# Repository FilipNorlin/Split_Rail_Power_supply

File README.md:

# PFC

# General Continuous-Time State-Space Form

$$
\dot{\mathbf{x}}(t) = A\mathbf{x}(t) + B\mathbf{u}(t)
$$
$$
\mathbf{y}(t) = C\mathbf{x}(t) + D\mathbf{u}(t)
$$

---

$$
	\underbrace{ \left(
		\begin{matrix}
		\dot{x}_{1}(t) \\
		\dot{x}_{2}(t) \\
		\dots \\
		\dot{x}_{n}(t)
		\end{matrix}
	\right) }_{ \dot{x}(t) }
	=
	\underbrace{ \left(
	\begin{matrix}
	A_{11}, A_{12} \dots A_{1n} \\
	A_{21}, A_{22} \dots A_{2n} \\
	\dots \\
	A_{n1}, A_{n2} \dots A_{nn}
	\end{matrix}
	\right) }_{ A }
	\underbrace{ \left(
	\begin{matrix}
	x_{1}(t) \\
	x_{2}(t) \\
	\dots \\
	x_{n}(t)
	\end{matrix}
	\right) }_{ x(t) }
	+ 
	\underbrace{ \left(
	\begin{matrix}
	B_{1} \\
	B_{2} \\
	\dots \\
	B_{n}
	\end{matrix}
	\right) }_{ B }	
	u(t)
$$

$$
y(t) = \underbrace{ [C_{1}, C_{2},\dots C_{n}] }_{ C } 
\underbrace{ \left(
\begin{matrix}
x_{1}(t) \\
x_{2}(t) \\
\dots \\
x_{n}(t)
\end{matrix}
\right) }_{ x(t) }
+
Du(t)
$$

# State Variables

## Large Signal Model

$$
\begin{align}
	x &= 
	\begin{bmatrix}
	i_{L_{A}}(t) \\
	i_{L_{B}}(t) \\
	v_{\text{out}}(t)
	\end{bmatrix}
	& \dot{x} = 
	\begin{bmatrix}
	\dot{i}_{L_{A}}(t) \\
	\dot{i}_{L_{B}}(t) \\
	\dot{v}_{\text{out}}(t)
	\end{bmatrix}
	&& u=v_{\text{in}}
	&& y=v_{\text{out}}
\end{align}
$$

The two switches are $180\degree$ out of phase. This means that the system will have 4 different states of operation. There will be a point where $\text{q}_{\text{A}}$ will be high and $\text{q}_{B}$ low and vise versa, if $\text{D}>0.5$ there will also be a point where both $\text{q}_{\text{A}}$ and $\text{q}_{B}$ will be high simultaneously. If $D < 0.5$  there will be a point where $\text{q}_{\text{A}}$ and $\text{q}_{\text{B}}$ both will be low simultaneously. This makes 4 states:

#### State 1: $\text{q}_{\text{A}}$ & $\text{q}_{\text{B}}$ are high

$$
\begin{align}
v_{L_{A}}(t) &= L \frac{di_{\text{L}_{A}}(t)}{dt} \implies \frac{di_{\text{L}_{A}}(t)}{dt} = \frac{v_{\text{in}}(t)}{L} \\ \\
v_{L_{B}}(t) &= L \frac{di_{\text{L}_{B}}(t)}{dt} \implies \frac{di_{\text{L}_{B}}(t)}{dt} = \frac{v_{\text{in}}(t)}{L} \\ \\
i_{c}(t) &= C \frac{d v_{c}(t)}{dt} \implies \frac{d v_{c}(t)}{dt} = \frac{i_{c}(t)}{C} = -\frac{v_{\text{out}}(t)}{RC}
\end{align}
$$

Both switches are turned on thus both inductors are getting magnetized. The capacitor isnt being charged at this point by any inductor meaning that it is only being discharged to the load, hence why the current is negative.

#### State 2: $\text{q}_{\text{A}}$ high & $\text{q}_{\text{B}}$ low

$$
\begin{align}
v_{L_{A}}(t) &= L \frac{di_{\text{L}_{A}}(t)}{dt} \implies \frac{di_{\text{L}_{A}}(t)}{dt} = \frac{v_{\text{in}}(t)}{L} \\ \\
v_{L_{B}}(t) &= L \frac{di_{\text{L}_{B}}(t)}{dt} \implies \frac{di_{\text{L}_{B}}(t)}{dt} = \frac{v_{\text{in}}(t) - v_{\text{out}}(t)}{L} \\ \\
i_{c}(t) &= C \frac{d v_{c}(t)}{dt} \implies \frac{d v_{c}(t)}{dt} = \frac{i_{c}(t)}{C} = \frac{i_{\text{L}_{B}}(t)}{C} -\frac{v_{\text{out}}(t)}{RC}
\end{align}
$$

Inductor A is still getting magnetized while inductor B is getting demagnetized. The energy from inductor B is being used to charge the output capacitor. 

#### State 3: $\text{q}_{\text{A}}$ low & $\text{q}_{\text{B}}$ high

$$
\begin{align}
v_{L_{A}}(t) &= L \frac{di_{\text{L}_{A}}(t)}{dt} \implies \frac{di_{\text{L}_{A}}(t)}{dt} = \frac{v_{\text{in}}(t) - v_{\text{out}}(t)}{L} \\ \\
v_{L_{B}}(t) &= L \frac{di_{\text{L}_{B}}(t)}{dt} \implies \frac{di_{\text{L}_{B}}(t)}{dt} = \frac{v_{\text{in}}(t)}{L} \\ \\
i_{c}(t) &= C \frac{d v_{c}(t)}{dt} \implies \frac{d v_{c}(t)}{dt} = \frac{i_{c}(t)}{C} = \frac{i_{\text{L}_{A}}(t)}{C} -\frac{v_{\text{out}}(t)}{RC}
\end{align}
$$

Now Inductor B is getting magnetized while inductor A is getting demagnetized. The energy from inductor A is being used to charge the output capacitor. 

#### State 4: $\text{q}_{\text{A}}$ low & $\text{q}_{\text{B}}$ low

$$
\begin{align}
v_{L_{A}}(t) &= L \frac{di_{\text{L}_{A}}(t)}{dt} \implies \frac{di_{\text{L}_{A}}(t)}{dt} = \frac{v_{\text{in}}(t) - v_{\text{out}}(t)}{L} \\ \\
v_{L_{B}}(t) &= L \frac{di_{\text{L}_{B}}(t)}{dt} \implies \frac{di_{\text{L}_{B}}(t)}{dt} = \frac{v_{\text{in}}(t) - v_{\text{out}}(t)}{L} \\ \\
i_{c}(t) &= C \frac{d v_{c}(t)}{dt} \implies \frac{d v_{c}(t)}{dt} = \frac{i_{c}(t)}{C} = \frac{i_{\text{L}_{A}}(t) + i_{\text{L}_{B}}(t)}{C} -\frac{v_{\text{out}}(t)}{RC}
\end{align}
$$

In this last state both the switches are off meaning that both the inductors are getting demagnetized into the capacitor. Having two or more inductors switching with some offset will make the capacitor get charged more frequently thus reducing the voltage ripple on the output.

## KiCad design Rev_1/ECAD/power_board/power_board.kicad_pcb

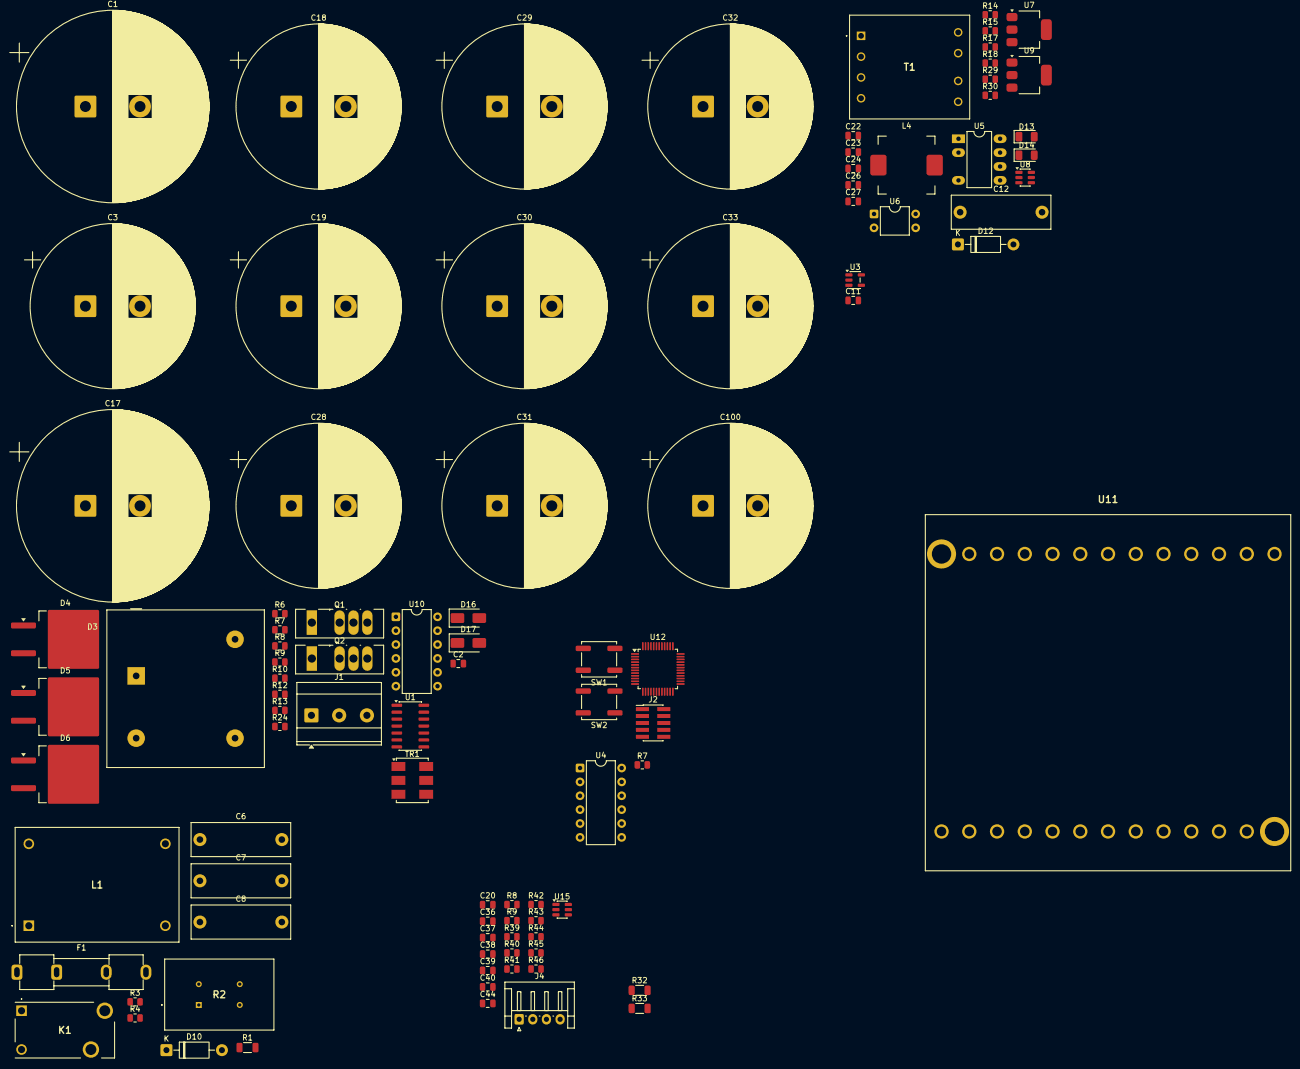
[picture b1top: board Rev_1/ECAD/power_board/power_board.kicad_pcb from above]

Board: 2 copper layers, 96 parts (0 on the bottom side), 57 nets, no tracks yet.

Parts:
C1, C17: 680u; CP_Radial_D35.0mm_P10.00mm_SnapIn
C2: 1u; C_0805_2012Metric
C3, C18, C19, C28, C29, C30, C31, C32, C33, C100: 2m2; CP_Radial_D30.0mm_P10.00mm_SnapIn
C6: 100n; C_Rect_L18.0mm_W6.0mm_P15.00mm_FKS3_FKP3
C7, C8: 2n2; C_Rect_L18.0mm_W6.0mm_P15.00mm_FKS3_FKP3
C11, C20, C36, C37, C38, C40, C44: 100n; C_0805_2012Metric
C12: 2n2, 250VAC; C_Rect_L18.0mm_W6.0mm_P15.00mm_FKS3_FKP3
C22, C26: 10u; C_0805_2012Metric
C23, C27: 22u; C_0805_2012Metric
C24: 100n, 16V; C_0805_2012Metric
C39: 4u7; C_0805_2012Metric
D3: KBPC3510W; Diode_Bridge_GeneSiC_KBPC_W
D4, D5, D6: schottky; TO-263-2
D10, D12: 1N4007; D_DO-41_SOD81_P10.16mm_Horizontal
D13, D14: D_Schottky; D_1206_3216Metric
D16, D17: BYG20J; D_SMA
F1: T6A3; Fuseholder_Clip-5x20mm_Keystone_3512_Inline_P23.62x7.27mm_D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
J1: Screw_Terminal_01x03; TerminalBlock_Phoenix_MKDS-3-3-5.08_1x03_P5.08mm_Horizontal
J2: Conn_ARM_JTAG_SWD_10; PinHeader_2x05_P1.27mm_Vertical_SMD
J4: Conn_01x04_Pin; JST_EH_S4B-EH_1x04_P2.50mm_Horizontal
K1: SPST-NO; Industrial-Relays-OJS-SS-112HEF_SPST-NO
L1: 2m2; Common_Mode_Choke_2Line
L4: 6u8; Inductor_SMD_Pulse_BPSC_10.5x10.3mm
Q1, Q2: IPZA60R070CM8XKSA1; TO-247-4_Vertical
R1: 22; R_1206_3216Metric
R2: 27; Resistor_THT_Power_Axial_WW20W_P27mm
R3, R15: 1k; R_0805_2012Metric
R4, R7, R7#2, R8, R8#2, R9, R12, R13, R24: 10k; R_0805_2012Metric
R6, R9#2, R30: 4k7; R_0805_2012Metric
R10: 3k3; R_0805_2012Metric
R14: 3.6M; R_0805_2012Metric
R17: 390 1/8W; R_0805_2012Metric
R18: 2k 1/8W; R_0805_2012Metric
R29: 34k; R_0805_2012Metric
R32, R33: 10k; R_1206_3216Metric
R39, R40, R41, R42, R43, R44, R45, R46: 5k1; R_0805_2012Metric
SW1, SW2: SW_Push; SW_Push_1P1T_NO_CK_KSC6xxJ
T1: 063932
TR1: ADT1-1WT; Mini-Circuits_CD542_H2.84mm
U1: UCC27714D; SOIC-14_3.9x8.7mm_P1.27mm
U3: INA180A4; SOT-23-5
U4, U10: PC837; DIP-12_W7.62mm
U5: TNY274P; PowerIntegrations_PDIP-8C
U6: PC817; DIP-4_W7.62mm
U7: 5V LDO; SOT-223-3_TabPin2
U8: LMR51430; SOT-23-6
U9: 3v3 LDO; SOT-223-3_TabPin2
U11: B66398W1024T1; ETD59
U12: STM32F103C8Tx; LQFP-48_7x7mm_P0.5mm
U15: USBLC6-2SC6; SOT-23-6

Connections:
+3V3_Secondary: C20.1, C27.1, C36.1, C37.1, C38.1, C39.1, C44.1, J2.1 (VTref), R8.1, R24.1, SW2.1, U9.3 (OUT), U12.9 (VDDA), U12.24 (VDD), U12.36 (VDD), U12.48 (VDD)
+5V: C11.1, U3.5 (V+)
+5V_Primary: C23.1, R6.1, R7.1, R9#2.1, R12.1, R13.1, U7.3 (OUT)
+5V_Secondary: C26.1, U9.1 (IN)
+12V: D10.1 (K), R1.1
+12V_Secondary: C22.1, D14.1 (K), U7.1 (IN), U8.3 (VIN), U8.5 (EN)
+70V: C18.1, C28.1, C30.1, C32.1, C100.1, R32.1
-70V: C3.2, C19.2, C29.2, C31.2, C33.2, R33.2
/AC_L: F1.1, J1.1
/AC_N: C6.2, J1.2, L1.2
/EN/NC: R7.2, R9#2.2, U1.4 (EN/NC), U4.8
/GATE_DRIVER_HI: R12.2, U1.1 (HI), U10.12
/GATE_DRIVER_LI: R13.2, U1.2 (LI), U10.10
/HS: D17.2 (A), Q2.3 (DS), U1.11 (HS)
/H_SW_NODE: Q2.2 (S), TR1.3
/Input Filter And Slow Start/AC_L_OUT: D3.4, K1.4 (NO), R2.2
/Input Filter And Slow Start/AC_N_OUT: C8.1, D3.2, L1.3
/Input Filter And Slow Start/COIL_GATE: R3.1, R4.1
/Input Filter And Slow Start/L_FILTERED: C7.1, K1.3 (COM), L1.4, R2.1
/LS: Q1.3 (DS), U1.5 (COM)
/L_SW_NODE: Q1.1 (D), TR1.1
/MCU/BOOT0: R8.2, R9.1, SW2.2, U12.44 (BOOT0)
/MCU/D+: U15.3 (I/O2), U15.4 (I/O2)
/MCU/D-: U15.1 (I/O1), U15.6 (I/O1)
/MCU/MISO: J4.3, U12.27 (PB14)
/MCU/MOSI: J4.4, U12.28 (PB15)
/MCU/SCK: J4.2, U12.26 (PB13)
/MCU/SWCLK: J2.4 (SWCLK/TCK), U12.37 (PA14)
/MCU/SWDIO: J2.2 (SWDIO/TMS), U12.34 (PA13)
/MCU/~RST: C40.1, J2.10 (~RESET), SW1.2, U12.7 (NRST)
/MCU/~SS: J4.1, U12.25 (PB12)
/Startup Power/BOOTSTRAP: C24.1, U8.6 (CB)
/Startup Power/BUCK_5V: L4.2, R29.1
/Startup Power/FB: R29.2, R30.1, U8.4 (FB)
/Startup Power/SW: C24.2, L4.1, U8.2 (SW)
/VREF: C2.1, R6.2, R10.1
/~ENABLE_GATE_DRIVER: U4.5, U10.3
Earth_Protective: C7.2, C8.2, J1.3
GND1: C1.2, C17.2, D3.3 (-), U5.5 (S), U5.6 (S), U5.7 (S), U5.8 (S), U6.3
GND2: D6.1 (A), D6.3 (K), TR1.2
unnamed: C6.1, F1.2, L1.1
unnamed: C3.1, C18.2, C19.1, C28.2, C29.1, C30.2, C31.1, C32.2, C33.1, C100.2, R32.2, R33.1
unnamed: D4.1 (A), D4.3 (K), TR1.6
unnamed: D4.2 (K), D5.2 (K), D6.2 (K)
unnamed: D5.3 (K), TR1.4
unnamed: D10.2 (A), K1.1 (COIL_1)
unnamed: D12.2 (A), T1.4, U5.4 (D)
unnamed: D12.1 (K), R15.2
unnamed: D13.2 (A), T1.5
unnamed: D14.2 (A), T1.6
unnamed: D16.1 (K), U1.13 (HB)
unnamed: K1.2 (COIL_2), R1.2
unnamed: R17.2, R18.1, U6.1
unnamed: R14.2, U5.1 (EN/UV), U6.4
PRIM_SGND: C2.2, C11.2, C12.2, C22.2, C23.2, R4.2, R7#2.2, R8#2.2, R10.2, R18.2, T1.8, U1.3 (VSS), U3.2 (GND), U4.7, U6.2, U7.2 (GND), U10.9, U10.11
SEC_SGND: C20.2, C26.2, C27.2, C36.2, C37.2, C38.2, C39.2, C40.2, C44.2, J2.3 (GND), J2.5 (GND), J2.9 (GNDDetect), R9.2, R30.2, SW1.1, T1.7, U4.6, U8.1 (GND), U9.2 (GND), U10.2, U10.4, U12.8 (VSSA), U12.23 (VSS), U12.35 (VSS), U12.47 (VSS), U15.2 (GND)
VBUS: C1.1, C12.1, C17.1, D3.1 (+), Q2.1 (D), R14.1, T1.1

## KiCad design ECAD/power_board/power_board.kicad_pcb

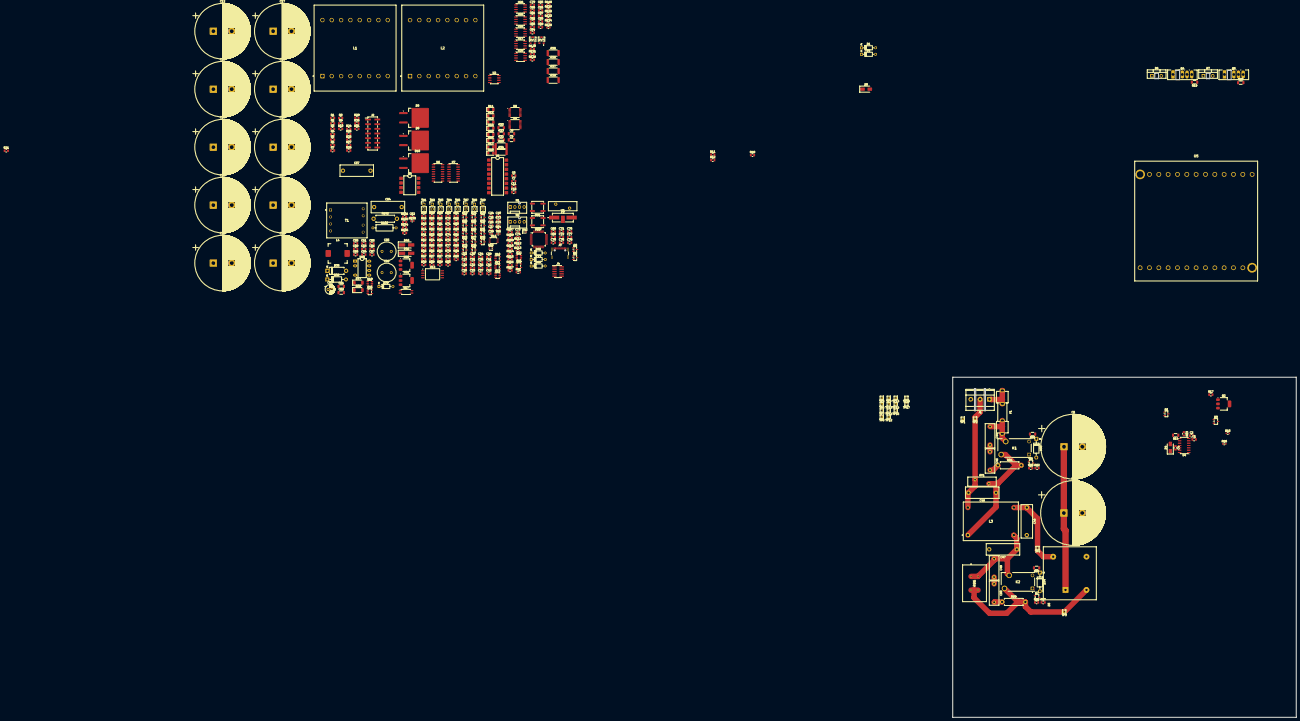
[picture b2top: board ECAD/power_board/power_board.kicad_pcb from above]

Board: 4 copper layers, 346 parts (0 on the bottom side), 217 nets.

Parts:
C1, C4, C6, C7, C10, C11, C28, C29, C34, C35, C38, C42, C43, C68, C69, C70, C71, C75, C76, C77, C78, C79, C82, C85, C86, C87: 100n; C_0805_2012Metric
C2, C22, C23, C30, C31, C32, C33, C36, C37, C41, C63, C65, C66, C80, C81, C84, C88, C89: 1u; C_0805_2012Metric
C3, C5: 680u; CP_Radial_D35.0mm_P10.00mm_SnapIn
C8, C9: C_Small; C_1206_3216Metric
C12, C13, C14, C15, C16, C17, C18, C19, C20, C21: 2m2; CP_Radial_D30.0mm_P10.00mm_SnapIn
C24, C25, C26, C27: TBD; C_0603_1608Metric
C39, C40: 300p; C_0603_1608Metric
C44, C45, C49, C50: 100n, >230Vac; C_Rect_L13.0mm_W5.0mm_P10.00mm_FKS3_FKP3_MKS4
C46: 100n, >230AC; C_Rect_L18.0mm_W6.0mm_P15.00mm_FKS3_FKP3
C47, C48, C57: 2n2; C_Rect_L18.0mm_W6.0mm_P15.00mm_FKS3_FKP3
C51: 10n, 1kV; C_1206_3216Metric
C52: 100n, 50V; C_0603_1608Metric
C53: 10u, 50V; CP_Radial_D5.0mm_P2.00mm
C54: 2n2, 250VAC; C_Rect_L18.0mm_W6.0mm_P15.00mm_FKS3_FKP3
C55, C56: 470u; C_Radial_D10.0mm_H16.0mm_P5.00mm
C58: 4u7, 20V; C_0805_2012Metric
C59, C64, C83: 10u; C_0805_2012Metric
C60, C67: 22u; C_0805_2012Metric
C61: 100n, 16V; C_0805_2012Metric
C62: 47u; C_1206_3216Metric
C72: 4u7; C_0805_2012Metric
C73, C74: 27p; C_0603_1608Metric
D1, D2, D43, D44, D45: 1N4148; D_DO-35_SOD27_P7.62mm_Horizontal
D3: KBPC3510W; Diode_Bridge_GeneSiC_KBPC_W
D4, D5: BYG20J; D_SMA
D6, D7: D; TO-220-2_Vertical
D8, D9, D10: schottky; TO-263-2
D11, D12, D13, D14, D15, D16, D17, D18: LED; LED_1206_3216Metric
D19, D20, D21, D22, D23, D24, D25, D26, D27, D28, D29, D30, D31, D32: BAT54S; SOT-23
D33, D34, D36: 1N4007; D_DO-41_SOD81_P10.16mm_Horizontal
D35: P6KE150A; D_DO-15_P10.16mm_Horizontal
D37, D38: SB24; D_SOD-128
D39: BZX79-C11; D_DO-35_SOD27_P7.62mm_Horizontal
D40, D41: SK15; D_SMA_Handsoldering
D42: TVS; D_SOD-523
F1: T6A3; Fuseholder_Clip-5x20mm_Keystone_3512_Inline_P23.62x7.27mm_D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
F2: Polyfuse; RV_Disc_D15.5mm_W5mm_P7.5mm
FB1: 120R; L_0805_2012Metric
J1: Screw_Terminal_01x03; TerminalBlock_Phoenix_MKDS-3-3-5.08_1x03_P5.08mm_Horizontal
J2: Conn_02x07_Odd_Even; PinHeader_2x07_P2.54mm_Vertical_SMD
J3: USB_C_Receptacle_USB2.0_16P; USB_C_Receptacle_GCT_USB4105-xx-A_16P_TopMnt_Horizontal
J4: Conn_ARM_JTAG_SWD_10; PinHeader_2x05_P1.27mm_Vertical_SMD
K1, K2: SPST-NO; Industrial-Relays-OJS-SS-112HEF_SPST-NO
L1, L2: 220u; ETD-39-Inductor
L3: 2m2; Common_Mode_Choke_2Line
L4: 6u8; Inductor_SMD_Pulse_BPSC_10.5x10.3mm
M1, M2: Fan_4pin; FanPinHeader_1x04_P2.54mm_Vertical
Q1: NPN; SOT-23
Q2: NMOS; SOT-223-3_TabPin2
Q3, Q6, Q7: NMOS; SOT-23-3
Q4, Q5: IPZA60R070CM8XKSA1; TO-247-4_Vertical
Q8, Q9: 2N7002; SOT-23
R1, R2, R3, R4, R5: 330; R_0805_2012Metric
R6, R7, R8, R9, R10, R49, R50, R51, R52, R53, R54, R76, R92, R97, R101, R120, R126: 1k; R_0805_2012Metric
R11, R106: 4k7; R_0805_2012Metric
R12, R121: 100k; R_0805_2012Metric
R13: 5; R_0805_2012Metric
R14: 2.2; R_1206_3216Metric
R15, R16: 0; R_0603_1608Metric
R17, R18: 470; R_0805_2012Metric
R19, R20: 3, 1W; R_1206_3216Metric
R21: 10m; R_0805_2012Metric
R22, R23: R_Small; R_1206_3216Metric
R24, R25, R26, R27, R28, R29, R30, R31, R109, R110: 5k1; R_0805_2012Metric
R32: 15m; R_1206_3216Metric
R33, R34, R35, R36, R37, R38: 10k, 1W; R_2512_6332Metric
R39, R40, R45, R46, R47, R48, R55, R56, R57, R58, R59, R63, R64, R65, R66, R67, R70, R71, R72, R74, R77, R78, R88, R89, R90: 3k3; R_0805_2012Metric
R41, R42, R43, R44: 100; R_0805_2012Metric
R60, R61, R62, R85, R86, R87: 27k; R_0805_2012Metric
R68, R69, R93, R98, R107, R108, R114, R115, R116, R117: 10k; R_0805_2012Metric
R73, R75: 22k; R_0603_1608Metric
R79, R80, R81, R82, R83: 68k; R_0805_2012Metric
R84, R118, R119, R122, R123, R124, R125: R_Small; R_0603_1608Metric
R91, R95: 22; R_1206_3216Metric
R94, R99: 100, >230Vac; R_Axial_DIN0411_L9.9mm_D3.6mm_P12.70mm_Horizontal
R96: 27; Resistor_THT_Power_Axial_WW20W_P27mm
R100: 3.6M, 325V; R_Axial_DIN0309_L9.0mm_D3.2mm_P12.70mm_Horizontal
R102: 100, 325V; R_Axial_DIN0411_L9.9mm_D3.6mm_P12.70mm_Horizontal
R103: 390 1/8W; R_0805_2012Metric
R104: 2k 1/8W; R_0805_2012Metric
R105: 34k; R_0603_1608Metric
R111, R112: 22; R_0603_1608Metric
R113: 1k5; R_0603_1608Metric
RV1: Varistor; RV_Disc_D15.5mm_W5mm_P7.5mm
RV2, RV3: 100k; Potentiometer_SMD_Trimmer_PVG3_3.6x3
SW1, SW2: SW_Push; SW_Push_1P1T_NO_CK_KSC6xxJ
T1: 063932
TH1, TH2, TH3, TH4, TH5, TH7, TH8, TH9: 10k; PinHeader_1x02_P2.54mm_Vertical
TH6: 10k; R_0603_1608Metric
TP1: LIVE_IN; Pin_D0.7mm_L6.5mm_W1.8mm_FlatFork
TP2: NEUTRAL_IN; Pin_D0.7mm_L6.5mm_W1.8mm_FlatFork
TP3: LIVE_OUT; Pin_D0.7mm_L6.5mm_W1.8mm_FlatFork
TP4: NEUTRAL_OUT; Pin_D0.7mm_L6.5mm_W1.8mm_FlatFork
TP5: HG; Pin_D0.7mm_L6.5mm_W1.8mm_FlatFork
TP6: VBUS; Pin_D0.7mm_L6.5mm_W1.8mm_FlatFork
TP7: LG; Pin_D0.7mm_L6.5mm_W1.8mm_FlatFork
TP8: HP; Pin_D0.7mm_L6.5mm_W1.8mm_FlatFork
TP9: LP; Pin_D0.7mm_L6.5mm_W1.8mm_FlatFork
TP10: HS; Pin_D0.7mm_L6.5mm_W1.8mm_FlatFork
TP11: LS; Pin_D0.7mm_L6.5mm_W1.8mm_FlatFork
TP12: +RECT; Pin_D0.7mm_L6.5mm_W1.8mm_FlatFork
TP13: -RECT; Pin_D0.7mm_L6.5mm_W1.8mm_FlatFork
TP14: +70V; Pin_D0.7mm_L6.5mm_W1.8mm_FlatFork
TP15: -70V; Pin_D0.7mm_L6.5mm_W1.8mm_FlatFork
TP16: PRIM_SHUNT_H; Pin_D0.7mm_L6.5mm_W1.8mm_FlatFork
TP17: PRIM_SHUNT_L; Pin_D0.7mm_L6.5mm_W1.8mm_FlatFork
U1: LTV-847S; SMDIP-16_W9.53mm
U2: ISO6720BD; SOIC-8_3.9x4.9mm_P1.27mm
U3: LTV-827S; SMDIP-8_W9.53mm
U4: UCC27714D; SOIC-14_3.9x8.7mm_P1.27mm
U5: ETD59
U6, U7: 74HC595; SOIC-16_3.9x9.9mm_P1.27mm
U8, U9: NMUX1308PW; TSSOP-16_4.4x5mm_P0.65mm
U10: INA180A2; SOT-23-5
U11: INA180A1; SOT-23-5
U12: AMC1350; SOT-23-6
U13: AMC1350DWV; SOIC-8_7.5x5.85mm_P1.27mm
U14: LM358; TSSOP-8_3x3mm_P0.65mm
U15: TLV6001DCK; SOT-353_SC-70-5
U16: TNY274P; PowerIntegrations_PDIP-8C
U17: PC817; SOP-4_4.4x2.6mm_P1.27mm
U18: 5V LDO; SOT-223-3_TabPin2
U19: LMR51430; SOT-23-6
U20: TPS60403DBV; SOT-23-5
U21: 3v3 LDO; SOT-223-3_TabPin2
U22: USBLC6-2SC6; SOT-23-6
U23: STM32F103C8Tx; LQFP-48_7x7mm_P0.5mm
U24: TPS3823-xxDBV; SOT-23-5
U25, U25#2, U27, U28: LMV393; SOIC-8_3.9x4.9mm_P1.27mm
U26: NE555D; SOIC-8_3.9x4.9mm_P1.27mm
Y1: 8MHz; HC-49US

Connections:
+3V3_Secondary: C6.1, C7.1, C10.1, C11.1, C29.1, C35.1, C67.1, C68.1, C69.1, C70.1, C71.1, C72.1, C78.1, C86.1, C87.1, D19.2 (K), D20.2 (K), D21.2 (K), D22.2 (K), D23.2 (K), D24.2 (K), D25.2 (K), D27.2 (K), D28.2 (K), D29.2 (K), D30.2 (K), D31.2 (K), J4.1 (VTref), R9.1, R10.1, R39.1, R40.1, R47.1, R48.1, R57.1, R58.1, R66.1, R67.1, R77.1, R107.1, R113.1, R122.1, R124.1, RV3.1, SW2.1, U2.1 (VCC1), U6.10 (~SRCLR), U6.16 (VCC), U7.10 (~SRCLR), U7.16 (VCC), U8.16 (V_{CC}), U9.16 (V_{CC}), U11.5 (V+), U14.8 (V+), U15.5 (V+), U21.3 (OUT), U23.9 (VDDA), U23.24 (VDD), U23.36 (VDD), U23.48 (VDD), U24.5 (V_{DD}), U27.8 (V+), U28.8 (V+)
+5V_Primary: C28.1, C60.1, C79.1, C82.1, C85.1, D32.2 (K), R6.1, R7.1, R8.1, R118.1, R121.1, RV2.1, U2.8 (VCC2), U10.5 (V+), U12.5 (S), U13.1 (VDD1), U18.3 (OUT), U25.8 (V+), U25#2.8 (V+), U26.4 (~RST), U26.8 (VCC)
+5V_Secondary: C62.1, C63.1, C64.1, D40.1 (K), D41.1 (K), R116.1, R117.1, U13.8 (VDD2), U20.2 (IN), U21.1 (IN)
+5V_USB: C77.1, D40.2 (A), FB1.2
+12V_Primary: C55.1, C59.1, D33.1 (K), D34.1 (K), D37.1 (K), D39.1 (K), R13.1, R91.1, R95.1, U18.1 (IN)
+12V_Secondary: C56.1, C58.1, D38.1 (K), M1.2 (+), M2.2 (+), U19.3 (VIN), U19.5 (EN)
+70V: C12.1, C14.1, C16.1, C18.1, C20.1, L1.2, R33.1, R35.1, R37.1, R85.1, TP14.1 (1_1)
-5V: C38.1, C66.1, D26.1 (A), U14.4 (V-), U20.1 (OUT)
-70V: C13.2, C15.2, C17.2, C19.2, C21.2, L2.2, R34.2, R36.2, R38.2, R62.1, TP15.1 (1_1)
/AC_L: F1.1, J1.1, TP1.1 (1_1)
/AC_N: C46.2, J1.2, L3.2, RV1.2, TP2.1 (1_1)
/Current Sensing/+: C25.1, R41.2, U11.3 (+)
/Current Sensing/-: C27.1, R42.2, U11.4 (-)
/Current Sensing/AD_TEMP_BOARD: D25.3 (COM), R64.2, U8.13 (Y0)
/Current Sensing/AD_TEMP_DIODE1: D19.3 (COM), R45.2, U8.14 (Y1)
/Current Sensing/AD_TEMP_DIODE2: D22.3 (COM), R55.2, U8.15 (Y2)
/Current Sensing/AD_TEMP_DIODE3: D24.3 (COM), R63.2, U8.12 (Y3)
/Current Sensing/AD_TEMP_DIODE_PRIM1: D27.3 (COM), R70.2, U8.4 (Y7)
/Current Sensing/AD_TEMP_DIODE_PRIM2: D30.3 (COM), R78.2, U9.13 (Y0)
/Current Sensing/AD_TEMP_NMOS_HS: D23.3 (COM), R56.2, U8.1 (Y4)
/Current Sensing/AD_TEMP_NMOS_LS: D20.3 (COM), R46.2, U8.5 (Y5)
/Current Sensing/AD_TEMP_TANSFORMER: D28.3 (COM), R71.2, U8.2 (Y6)
/Current Sensing/HW Protection/PRIM_CURRENT_VREF: C81.1, RV2.2, U25.2 (-)
/Current Sensing/HW Protection/SEC_CURRENT_VREF: C88.1, RV3.2, U28.2 (-)
/Current Sensing/HW Protection/~TRIG: U25.1, U26.2 (TRIG)
/Current Sensing/MUX_OUT: C40.1, R75.2, U15.4, U23.10 (ADC1_IN0)
/Current Sensing/PRIMARY_CURRENT_SENSE: R49.1, U10.1
/Current Sensing/PRIMARY_MUX_OUT: U12.4 (A), U13.2 (IN+)
/Current Sensing/PRIM_BUS_VOLTAGE: D32.3 (COM), R89.2, U12.3 (B1), U25.5 (+), U25#2.3 (+)
/Current Sensing/PRIM_CURRENT_SENSE: R49.2, R50.1, U12.1 (B2), U25.3 (+)
/Current Sensing/SECONDARY_CURRENT_SENSE: R52.1, U11.1
/Current Sensing/SEC_CURRENT_SENSE: D21.3 (COM), R52.2, R53.1, U28.3 (+)
/Current Sensing/SEC_NEG_VOLTAGE: D29.3 (COM), R76.2, U27.5 (+)
/Current Sensing/SEC_POS_VOLTAGE: D31.3 (COM), R90.2, U27.3 (+)
/EN/NC: Q1.1 (C), U4.4 (EN/NC)
/GATE_DRIVER_HI: U2.2 (INA), U23.29 (TIM1_CH1)
/GATE_DRIVER_HI_ISO: U2.7 (OUTA), U4.1 (HI)
/GATE_DRIVER_LO: U2.3 (INB), U23.30 (TIM1_CH2)
/GATE_DRIVER_LO_ISO: U2.6 (OUTB), U4.2 (LI)
/HG: Q4.4 (G), R19.2
/HS: C4.1, D5.2 (A), Q4.3 (DS), U4.11 (HS)
/H_SW: R19.1, TP5.1 (1_1), U4.12 (HO)
/H_SW_NODE: D6.1 (K), Q4.2 (S), TP8.1 (1_1), U5.13 (P1)
/Input Filter And Slow Start/AC_L_FILTERED: C47.1, C49.1, K2.3 (COM), L3.4, R96.1
/Input Filter And Slow Start/AC_L_FUSED: C44.1, F1.2, K1.3 (COM)
/Input Filter And Slow Start/AC_L_INPUT_RELAY: C46.1, K1.4 (NO), L3.1, R94.2, RV1.1
/Input Filter And Slow Start/AC_L_OUT: D3.4, K2.4 (NO), R96.2, R99.2, TP3.1 (1_1)
/Input Filter And Slow Start/AC_N_OUT: C48.1, D3.2, L3.3, TP4.1 (1_1)
/Input Filter And Slow Start/AC_RELAY1_RC_SNUBBER_1: C44.2, C45.1
/Input Filter And Slow Start/AC_RELAY1_RC_SNUBBER_2: C45.2, R94.1
/Input Filter And Slow Start/AC_RELAY2_RC_SNUBBER_1: C49.2, C50.1
/Input Filter And Slow Start/AC_RELAY2_RC_SNUBBER_2: C50.2, R99.1
/Input Filter And Slow Start/RELAY1_COIL_2: K1.2 (COIL_2), R91.2
/Input Filter And Slow Start/RELAY2_COIL_2: K2.2 (COIL_2), R95.2
/Input Filter And Slow Start/RELAY_SWITCH_D: D33.2 (A), K1.1 (COIL_1), Q6.1 (D)
/Input Filter And Slow Start/RELAY_SWITCH_G: Q6.2 (G), R92.1, R93.1
/Input Filter And Slow Start/SOFT_SWITCH_D: D34.2 (A), K2.1 (COIL_1), Q7.1 (D)
/Input Filter And Slow Start/SOFT_SWITCH_G: Q7.2 (G), R97.1, R98.1
/LG: Q5.4 (G), R20.2
/LS: Q5.3 (DS), U4.5 (COM)
/L_SW: R16.1, R20.1, TP7.1 (1_1), U4.6 (LO)
/L_SW_NODE: D7.2 (A), Q5.1 (D), TP9.1 (1_1), U5.1 (P2)
/MCU/BOOT0: R107.2, R108.1, SW2.2, U23.44 (BOOT0)
/MCU/CC1: J3.A5 (CC1), R110.1
/MCU/CC2: J3.B5 (CC2), R109.1
/MCU/D+: J3.A6 (D+), J3.B6 (D+), R112.2, R113.2, U22.3 (I/O2), U22.4 (I/O2)
/MCU/D-: J3.A7 (D-), J3.B7 (D-), R111.2, U22.1 (I/O1), U22.6 (I/O1)
/MCU/FAN_PWM_1: Q8.1 (G), R114.1, U23.45 (TIM4_CH3)
/MCU/FAN_PWM_2: Q9.1 (G), R115.1, U23.46 (TIM4_CH4)
/MCU/POLLYFUSED: C76.1, F2.2, FB1.1
/MCU/PWM_1: M1.4 (PWM), Q8.3 (D), R116.2
/MCU/PWM_2: M2.4 (PWM), Q9.3 (D), R117.2
/MCU/RCC_OSC_IN: C73.2, U23.5 (RCC_OSC_IN), Y1.1
/MCU/RCC_OSC_OUT: C74.1, U23.6 (RCC_OSC_OUT), Y1.2
/MCU/STM_D+: R112.1, U23.33 (USB_DP)
/MCU/STM_D-: R111.1, U23.32 (USB_DM)
/MCU/SWCLK: J4.4 (SWCLK/TCK), U23.37 (SYS_JTCK-SWCLK)
/MCU/SWDIO: J4.2 (SWDIO/TMS), U23.34 (SYS_JTMS-SWDIO)
/MCU/TACHO_1: M1.3 (Tacho), U23.40 (TIM3_CH1)
/MCU/TACHO_2: M2.3 (Tacho), U23.41 (TIM3_CH2)
/MCU/TIM1_BKN: D43.1 (K), D44.1 (K), D45.1 (K), U23.16 (TIM1_BKIN)
/MCU/WDI: U23.31 (PA10), U24.4 (WDI)
/MCU/~MR: SW1.2, U24.3 (~MR)
/MCU/~RST: C75.2, J4.10 (~RESET), U23.7 (NRST), U24.1 (~RESET)
/NEG_RECTIFIED: D8.1 (A), D9.1 (A), D10.1 (A), L2.1, R23.2, TP13.1 (1_1)
/NEG_SNUB: C9.2, R23.1
/POS_RECTIFIED: D8.2 (K), D9.2 (K), D10.2 (K), L1.1, R22.2, TP12.1 (1_1)
/POS_SNUB: C8.2, R22.1
/PRIM_MUX_SELECT: R1.1, U23.18 (PB0)
/QH': U6.9 (QH'), U7.14 (SER)
/RCLK: U6.12 (RCLK), U7.12 (RCLK), U23.42 (PB6)
/RELAY_SOFT_SWITCH: R2.1, U23.19 (PB1)
/RELAY_SWITCH: R3.1, U23.20 (PB2)
/S10: U6.15 (QA), U8.11 (S0)
/S11: U6.1 (QB), U8.10 (S1)
/S12: U6.2 (QC), U8.9 (S2)
/S20: U6.4 (QE), U9.11 (S0)
/S21: U6.5 (QF), U9.10 (S1)
/S22: U6.6 (QG), U9.9 (S2)
/SEC_PRIM: C8.1, D8.3 (K), TP10.1 (1_1), U5.14 (S1)
/SEC_SEC: C9.1, D9.3 (K), TP11.1 (1_1), U5.26 (S2)
/SER: U6.14 (SER), U23.21 (PB10)
/SRCLK: U6.11 (SRCLK), U7.11 (SRCLK), U23.22 (PB11)
/Startup Power/AUX_PRIM: D37.2 (A), T1.5
/Startup Power/AUX_SEC: D38.2 (A), T1.6
/Startup Power/BOOTSTRAP: C61.1, U19.6 (CB)
/Startup Power/BUCK_5V: D41.2 (A), L4.2, R105.1
/Startup Power/FB: R105.2, R106.1, U19.4 (FB)
/Startup Power/SW: C61.2, L4.1, U19.2 (SW)
/TEMP_MUX1: U8.3 (Z), U23.14 (ADC1_IN4)
/TEMP_MUX2: U9.3 (Z), U23.15 (ADC1_IN5)
/Y1: J2.1, U9.14 (Y1)
/Y2: J2.3, U9.15 (Y2)
/Y3: J2.5, U9.12 (Y3)
/Y4: J2.7, U9.1 (Y4)
/Y5: J2.9, U9.5 (Y5)
/Y6: J2.11, U9.2 (Y6)
/Y7: J2.13, U9.4 (Y7)
/~E1: U6.3 (QD), U8.6 (~E)
/~E2: U6.7 (QH), U9.6 (~E)
/~PRIM_OCP: R9.2, U3.8, U23.17 (PA7)
/~PRIM_OVP: R10.2, U3.6, U23.38 (PA15)
/~RELAY_SOFT_SWITCH: R7.2, R97.2, U1.14
/~RELAY_SWITCH: R8.2, R92.2, U1.12
Earth_Protective: C47.2, C48.2, J1.3
GND1: C3.2, C5.2, C52.2, C53.2, C57.1, D3.3 (-), D6.2 (A), U16.5 (S), U16.6 (S), U16.7 (S), U16.8 (S), U17.3
unnamed: C22.1, R39.2, R45.1, TH1.1
unnamed: C23.1, R40.2, R46.1, TH2.1
unnamed: C30.1, R47.2, R55.1, TH3.1
unnamed: C31.1, R48.2, R56.1, TH4.1
unnamed: C32.1, R57.2, R63.1, TH5.1
unnamed: C33.1, R58.2, R64.1, TH6.1
unnamed: C34.1, R59.1, R60.2, R65.1
unnamed: C36.1, R66.2, R70.1, TH7.1
unnamed: C37.1, R67.2, R71.1, TH8.1
unnamed: C41.1, R77.2, R78.1, TH9.1
unnamed: C42.1, R83.2, R84.1, R89.1
unnamed: C43.1, R87.2, R88.1, R90.1
unnamed: C51.1, R102.2
unnamed: D1.1 (K), D2.1 (K), R11.1
unnamed: D4.2 (A), R14.2, R15.1
unnamed: C4.2, D4.1 (K), U4.13 (HB)
unnamed: D5.1 (K), Q2.1 (D)
unnamed: D11.2 (A), R24.2
unnamed: D12.2 (A), R25.2
unnamed: D13.2 (A), R26.2
unnamed: D14.2 (A), R27.2
unnamed: D15.2 (A), R28.2
unnamed: D16.2 (A), R29.2
unnamed: D17.2 (A), R30.2
unnamed: D18.2 (A), R31.2
unnamed: D26.3 (COM), R65.2, U14.3 (+)
unnamed: D35.2, R101.1
unnamed: D36.2 (A), T1.4, U16.4 (D)
unnamed: C51.2, D36.1 (K), R101.2
unnamed: D39.2 (A), R103.1
unnamed: Q1.2 (B), R11.2, R12.1
unnamed: Q2.2 (G), Q3.1 (D), R15.2, R17.1
unnamed: Q3.2 (G), R16.2, R18.1
unnamed: R1.2, U1.1
unnamed: R2.2, U1.3
unnamed: R3.2, U1.5
unnamed: R4.2, U3.1
unnamed: R5.2, U3.3
unnamed: R50.2, R51.1
unnamed: R53.2, R54.1
unnamed: R60.1, R61.2
unnamed: R61.1, R62.2
unnamed: R74.2, R76.1, U14.7
unnamed: R79.2, R80.1
unnamed: R80.2, R81.1
unnamed: R81.2, R82.1
unnamed: R82.2, R83.1
unnamed: R85.2, R86.1
unnamed: R86.2, R87.1
unnamed: R103.2, R104.1, U17.1
unnamed: R120.1, RV2.3
unnamed: R126.1, RV3.3
unnamed: C1.1, C2.1, R13.2, R14.1, U4.7 (VDD)
unnamed: R24.1, U7.15 (QA)
unnamed: R25.1, U7.1 (QB)
unnamed: R26.1, U7.2 (QC)
unnamed: R27.1, U7.3 (QD)
unnamed: R28.1, U7.4 (QE)
unnamed: R29.1, U7.5 (QF)
unnamed: R30.1, U7.6 (QG)
unnamed: R31.1, U7.7 (QH)
unnamed: C24.1, R43.2, U10.3 (+)
unnamed: C26.1, R44.2, U10.4 (-)
unnamed: R68.1, U13.7 (OUT+)
unnamed: R69.1, U13.6 (OUT-)
unnamed: R72.1, U14.1, U14.2 (-)
unnamed: R72.2, R74.1, U14.6 (-)
unnamed: C40.2, R68.2, R75.1, U15.1 (+)
unnamed: C39.1, R69.2, R73.1, U15.3 (-)
unnamed: C52.1, C53.1, U16.2 (BP/M)
unnamed: R100.2, U16.1 (EN/UV), U17.4
unnamed: C65.1, U20.5 (C_{FLY+})
unnamed: C65.2, U20.3 (C_{FLY-})
unnamed: C80.1, R118.2, R119.1, U25.6 (-)
unnamed: C83.1, R121.2, U26.6 (THRES), U26.7 (DISCH)
unnamed: C84.1, R122.2, R123.1, U27.2 (-)
unnamed: C89.1, R124.2, R125.1, U27.6 (-)
PRIM_OCP: D1.2 (A), R4.1, U26.3 (OUT)
PRIM_OVP: D2.2 (A), R5.1, U25.7, U25#2.1
PRIM_SGND: C1.2, C2.2, C24.2, C26.2, C28.2, C42.2, C54.2, C55.2, C57.2, C59.2, C60.2, C79.2, C80.2, C81.2, C82.2, C83.2, C85.2, D32.1 (A), Q1.3 (E), Q2.3 (S), Q3.3 (S), Q6.3 (S), Q7.3 (S), R12.2, R17.2, R18.2, R51.2, R84.2, R93.2, R98.2, R104.2, R119.2, R120.2, T1.8, U1.11, U1.13, U1.15, U2.5 (GND2), U3.2, U3.4, U4.3 (VSS), U10.2 (GND), U12.2 (GND), U13.3 (IN-), U13.4 (GND1), U17.2, U18.2 (GND), U25.4 (V-), U26.1 (GND)
PRIM_SHUNT_H: Q5.2 (S), R21.2, R43.1, TP16.1 (1_1)
PRIM_SHUNT_L: R21.1, R44.1, TP17.1 (1_1), U25#2.4 (V-)
SEC_NEG_OVP: D45.2 (A), U23.26 (PB13), U27.7
SEC_OCP: D43.2 (A), U23.2 (PC13), U28.1
SEC_POS_OVP: D44.2 (A), U23.25 (PB12), U27.1
SEC_SGND: C6.2, C7.2, C10.2, C11.2, C22.2, C23.2, C25.2, C27.2, C29.2, C30.2, C31.2, C32.2, C33.2, C34.2, C35.2, C36.2, C37.2, C38.2, C39.2, C41.2, C43.2, C56.2, C58.2, C62.2, C63.2, C64.2, C66.2, C67.2, C68.2, C69.2, C70.2, C71.2, C72.2, C73.1, C74.2, C75.1, C76.2, C77.2, C78.2, C84.2, C86.2, C87.2, C88.2, C89.2, D11.1 (K), D12.1 (K), D13.1 (K), D14.1 (K), D15.1 (K), D16.1 (K), D17.1 (K), D18.1 (K), D19.1 (A), D20.1 (A), D21.1 (A), D22.1 (A), D23.1 (A), D24.1 (A), D25.1 (A), D26.2 (K), D27.1 (A), D28.1 (A), D29.1 (A), D30.1 (A), D31.1 (A), D42.2 (A), J2.2, J2.4, J2.6, J2.8, J2.10, J2.12, J2.14, J3.A1 (GND), J3.A12 (GND), J3.B1 (GND), J3.B12 (GND), J3.SH (SHIELD), J4.3 (GND), J4.5 (GND), J4.9 (GNDDetect), M1.1 (-), M2.1 (-), Q8.2 (S), Q9.2 (S), R54.2, R59.2, R73.2, R88.2, R106.2, R108.2, R109.2, R110.2, R114.2, R115.2, R123.2, R125.2, R126.2, SW1.1, T1.7, TH1.2, TH2.2, TH3.2, TH4.2, TH5.2, TH6.2, TH7.2, TH8.2, TH9.2, U1.2, U1.4, U1.6, U2.4 (GND1), U3.5, U3.7, U6.8 (GND), U6.13 (~OE), U7.8 (GND), U7.13 (~OE), U8.8 (GND), U9.8 (GND), U11.2 (GND), U13.5 (GND2), U14.5 (+), U15.2 (V-), U19.1 (GND), U20.4 (GND), U21.2 (GND), U22.2 (GND), U23.8 (VSSA), U23.23 (VSS), U23.35 (VSS), U23.47 (VSS), U24.2 (GND), U27.4 (V-), U28.4 (V-), Y1.3
SEC_SHUNT_H: C12.2, C13.1, C14.2, C15.1, C16.2, C17.1, C18.2, C19.1, C20.2, C21.1, R32.2, R33.2, R34.1, R35.2, R36.1, R37.2, R38.1, R41.1
SEC_SHUNT_L: R32.1, R42.1
VBUS: C3.1, C5.1, C54.1, D3.1 (+), D7.1 (K), D35.1, Q4.1 (D), R79.1, R100.1, R102.1, T1.1, TP6.1 (1_1)
VBUS_USB: D42.1 (K), F2.1, J3.A4 (VBUS), J3.A9 (VBUS), J3.B4 (VBUS), J3.B9 (VBUS), U22.5 (VBUS)
~PRIM_MUX_SELECT: R6.2, U1.16

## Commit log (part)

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2026-04-16 Updated gitignore
2026-04-16 First rough sketch
2026-04-19 Added lt spice files
